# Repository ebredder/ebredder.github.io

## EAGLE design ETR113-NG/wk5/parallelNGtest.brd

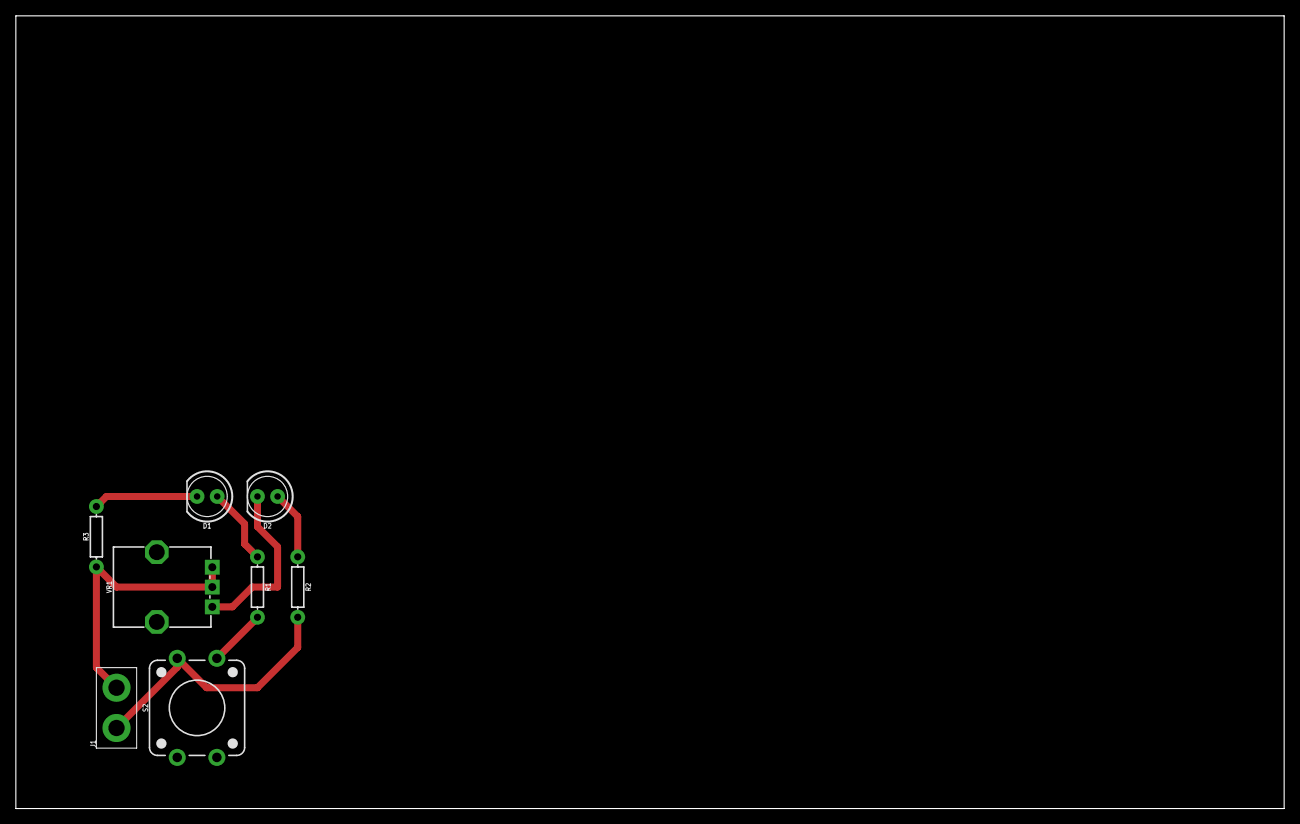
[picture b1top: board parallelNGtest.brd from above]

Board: 2 copper layers, 160.0 x 100.0 mm, 8 parts (0 on the bottom side), 7 nets.

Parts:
D1, D2: LED_5MM
J1: 1X02_XTRA_BIG
R1: 270; AXIAL-0.3
R2: ?; AXIAL-0.3
R3: 240; AXIAL-0.3
S2: SPST12mm; TACTILE_SWITCH_PTH_12MM
VR1: 100; POT-PTH-ALPS

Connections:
3.3V: J1.2, R3.P$1, VR1.P$2, VR1.P$3
12V: J1.1, R2.P$2, S2.3
unnamed: R1.P$2, S2.1
unnamed: D1.A, R1.P$1
unnamed: D2.A, R2.P$1
unnamed: D1.K, R3.P$2
unnamed: D2.K, VR1.P$1

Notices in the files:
parts and their libraries:
SparkFun-LED: Licensing: Creative Commons ShareAlike 4.0 International - https://creativecommons.org/licenses/by-sa/4.0
